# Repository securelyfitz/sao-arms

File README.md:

# sao-arms
addon extenders that look like arms, to be used along with [faces](https://github.com/securelyfitz/sao-faces) for a build-your-own badge. 
See the [microbadge](https://github.com/securelyfitz/microbadge) readme for more details about using them.

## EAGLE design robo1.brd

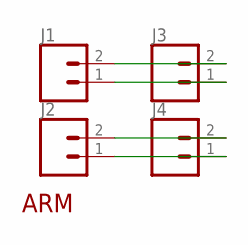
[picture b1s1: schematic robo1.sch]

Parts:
J1, J2, J3, J4: CONN_02LOCK; 1X02_LOCK
U$1: ARMROBO1; ROBOT1

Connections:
V1: J1.1, J3.1
V2: J1.2, J3.2
V3: J2.1, J4.1
V4: J2.2, J4.2

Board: 2 copper layers, 5 parts (0 on the bottom side), 4 nets, no tracks yet.

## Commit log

2018-08-09 adding schematic, board, cam, gerber and zip files for each arm style

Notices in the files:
parts and their libraries:
SparkFun-Connectors: Licensing: Creative Commons ShareAlike 4.0 International - https://creativecommons.org/licenses/by-sa/4.0
